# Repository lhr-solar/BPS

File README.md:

# Battery Protection System Code
This repo contains all code related to LHR Solar's Battery Protection System (BPS)
The [Documentation](https://bps.readthedocs.io/en/latest/) for the BPS contains other useful software and an in depth explanation of our architecture.

NOTE: As of 2023, the simulator for the BPS repository is deprecated.

## Setup
Development is done in a Linux environment to build and flash the BPS program.

### Cloning the Repo
Cloning repos onto your machine is usually straightforward, but our RTOS project depend on uCOS-III-Simulator and uCOS-III-STM32F4 repos. Extra steps must be taken to correctly pull submodules. [Submodules](https://git-scm.com/book/en/v2/Git-Tools-Submodules) are repos that are inside a repo.

The most common way to clone repos is to use the HTTPS link, but the most secure way is to clone with SSH. The submodules use SSH, so you must generate and add an SSH key to your GitHub account. Follow the instructions in this tutorial. If this is your first time doing this, you can start at the [Generating a new SSH key and adding it to the ssh-agent](https://docs.github.com/en/github/authenticating-to-github/generating-a-new-ssh-key-and-adding-it-to-the-ssh-agent) step, but reading everything is beneficial.

Once you're able to use Git with SSH, go to the green "Code" button of the repo, and click "Use SSH" to get the URL. Copy the `git@hithub.com:repo-name` link. Then, enter the following command to the terminal but with the correct URL:

```
git clone --recurse-submodules git@github.com:repo-name
```
If you already cloned the repo but don't have the submodules, enter the following commands:

```
git submodule init
git submodule update --remote
```

### Setup for Terminal Development
The BPS is designed be built and deployed from a Linux terminal, allowing you to use your choice of text editor/IDE.
1. Ensure that you have some type of Linux machine such as Ubuntu, Windows Subsystem for Linux, etc. Windows will not work.
    - While you can compile the code on WSL, you will not be able to flash the code unless it is through a Linux machine (VM, dual boot, etc.)
2. The BPS code supports multiple microcontrollers and different architectures. Depending on which on you're using, make sure you have the correct toolchain.
    - STM32F413: Follow the instructions in this [repo](https://github.com/SijWoo/ARM-Toolchain-Setup) to setup the toolchains for the current BPS.
    - Simulator: Install GCC and GDB using the following lines
        ```
        sudo apt install gcc gdb
        ```
3. (Optional) Download [VSCode](https://code.visualstudio.com/)
4. (Optional) In VSCode, download the following extensions (Click on the block icon on the left column):
    - C/C++
    - ARM
    - cortex-debug
5. OPTIONAL: If you are testing on the simulator, you must add the following line in `/etc/security/limits.conf` then restart your machine:
    ```
    <username>             -      rtprio          unlimited
    ```
    The tabbing MUST MATCH the other dashes at the bottom of the file, otherwise this will not work!

## Building
Run `make help` for more information on usage. 
When calling any of the following commands, make sure you are in the top level of the repo.

Call `make bsp_type` to compile the release version of the code. `bsp_type` is the system you want to compile for. It can either be
`stm32f4132` or `simulator`. The stm32f413 version is selected by default.

Call `make help` for more information on how to build the project.

Call `make clean` if the build fails for any reason other than syntax related.

The BPS has an RTOS version and a bare metal version for its BSP files. To select which one to build, pass either `RTOS` or `BAREMETAL` to the `OS` argument. For example
```
make simulator OS=BAREMETAL
```
will build the bare metal version, and  
```
make simulator OS=RTOS
```
will build the RTOS version. The RTOS version is selected by default.

The BPS configuration settings can be modified from the command line from Make. In the top-level of the repo,
you can specify `DEFINES=` alongside the `make` command to override values from the configuration
header file with the values you specify. For example
```
make test=Voltage DEFINES=NUM_MINIONS=2
```
Would update the BPS build to use 2 minion boards in the code and calculations as opposed to 3.
Run `make help` for more information on usage.

For testing, please read the Testing section.

### How to build a test
To build a new test, you need to use the following command:
`make bsp_type TEST=x`

- `x` specifies which test you want to compile. TEST= is optional and only required if a test is to be compiled. Set TEST equal to the suffix of the Test_ Src files i.e. if the test you want to run is in Test_x.c, set TEST=x.
    E.g. Call `make stm32f413 TEST=Voltage` if you want to test Voltage.c with the Test_Voltage.c src file

## Flashing
When calling any of the following commands, make sure you are in the top most level of the directory.
You must be on a Linux VM or dual boot machine. Consider using [VMWARE](https://kb.vmware.com/s/article/2057907) 
using this free license [key](https://gist.github.com/williamgh2019/cc2ad94cc18cb930a0aab42ed8d39e6f)

1. Install `st-util`
2. Connect your computer to the BPS using a Nucleo programmer
3. Call `make flash` to flash the most recently built BPS code. You may need to run this with `sudo`.

## Testing
The following testing information is specifically for terminal development.

### Rules for making a new test Src file
1. Test names: The formatting of the file names is crucial to have the Makefile work properly. "Test_" should be the prefix and the src file name that is to be tested must follow i.e. if you want to test x.c, the test Src file must be named Test_x.c or the Makefile will not be able to find the file.
    E.g. A test for Voltage.c should be Test_Voltage.c file, a test for BSP_SPI.c should be named Test_BSP_SPI.c
2. All test files should be placed into the Tests folder.

### Using GDB with OPENOCD
OpenOCD is a debugger program that is open source and compatible with the STM32F413. 
GDB is a debugger program that can be used to step through a program as it is being run on the board. To use, you need two terminals open, as well as a USB connection to the ST-Link programmer (as if you were going to flash the program to the board). 
1. Run `./openocd-debug.sh` in one terminal.
2. In the other terminal, start gdb with the command `gdb-multiarch ./Objects/bps-leader.elf` (assuming that you are doing this in the root of the project directory.
3. This will launch GDB and read in all of the symbols from the program that you are running on the board. In order to actually connect gdb to the board, execute the command `target extended-remote localhost:4242`, which will connect to the st-util command from earlier.

**Note:** If you get an error message for Permission denied, try giving openocd read/write permissions using chmod: `chmod 764 openocd`

https://linuxcommand.org/lc3_lts0090.php

### Using the Simulator
The simulator reads input from a JSON file to simulate dummy values and dumps output to a log file to simulate controlling the BPS's peripherals. The goal is to create repeatable tests that can be checked automatically by using the same test file, and by parsing the log file.

The simulator can be compiled with `make simulator`. The simulator also has an optional command line argument `TEST=` to specify the name of the test file to run. 

Note: when typing name it, don't type the `Test_` part or the `.c` part.

Example: `make simulator TEST=SimulatorInit`.

The simulator can be run with `./bps-simulator.out <path to JSON test>`. However, in order to run properly, `ulimit -r` must be set from within a script. In order to debug, edit the `test.sh` file
to either debug, or just run a specific test.

You can check the log file by doing `cat bps-sim-<logged time>.log`.

## Rules
Commit frequently into your own branches. Create a Pull Request whenever you are ready to add you working code to the master branch. Make sure that your code compiles without any errors or warnings before you open a pull request. At least one approver must approve your pull request before it can be merged. The reviewers will make sure everything is up to par with the coding standards.

### Code Reviews
You can review a pull request even if you are not an approver. In addition to helping us catch bugs, code reviews are a good opportunity to learn more about the BPS codebase. Some examples on what you can include in a code review are:
- Ask why the author wrote a certain part of code in a way they did
- Point out potential bugs in the code
- Point out that part of the code is not well documented or hard to read

You can either approve, comment, or request changes at the end of your pull request. These are the scenarios in which I would use each option:
- **Approve:** You are signing off that this pull request is ready to merge. You and the pull request author "own" this part of the code now.
- **Request Changes:** You have found problems with the code that must be addressed before it can be merged. Note that this will block the pull request from merging until you re-review the code.
- **Comment:** Do this if you do not want to explicitly approve or request changes.

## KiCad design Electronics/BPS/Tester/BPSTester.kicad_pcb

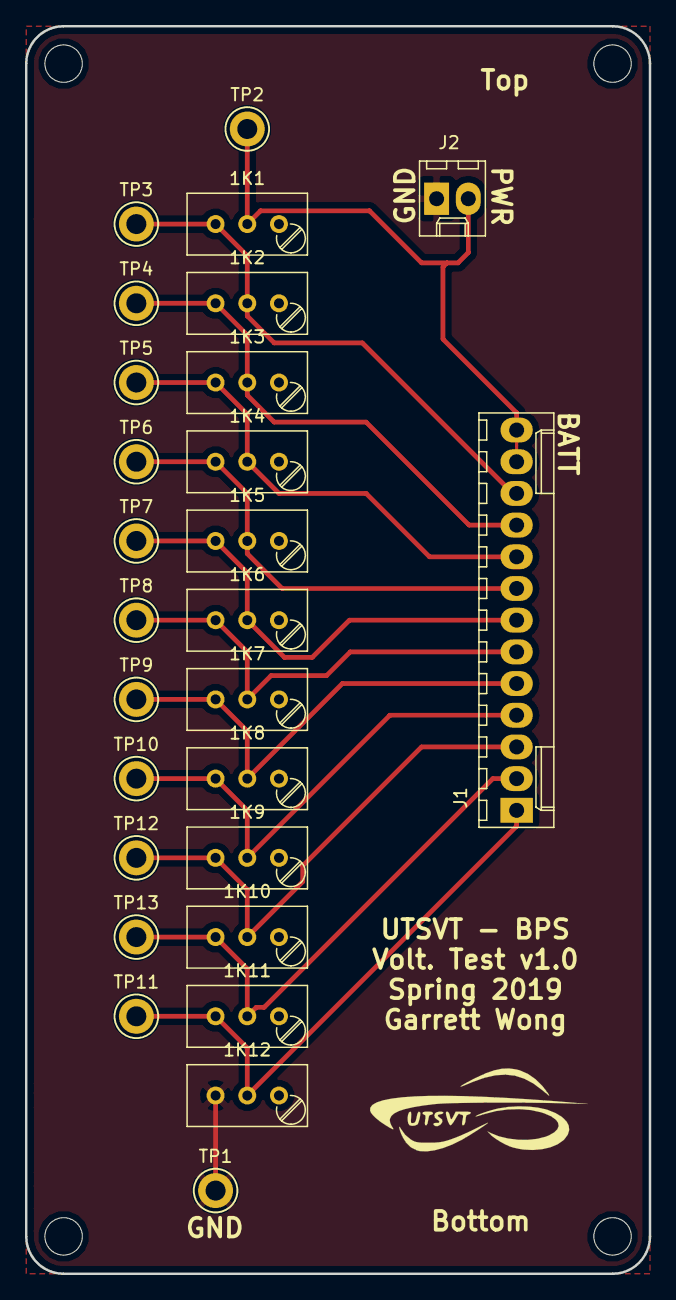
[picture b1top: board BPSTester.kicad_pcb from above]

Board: 2 copper layers, 50.0 x 100.0 mm, 27 parts (0 on the bottom side), 13 nets.

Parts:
1K1, 1K2, 1K3, 1K4, 1K5, 1K6, 1K7, 1K8, 1K9, 1K10, 1K11, 1K12: POT; Potentiometer_Trimmer_Bourns_3296W
J1: Conn_01x13_Male; Molex_KK-6410-13_13x2.54mm_Straight
J2: Conn_01x02_Male; Molex_KK-6410-02_02x2.54mm_Straight
TP1, TP2, TP3, TP4, TP5, TP6, TP7, TP8, TP9, TP10, TP11, TP12, TP13: TestPoint; Test_Point_Keystone_5005-5009_Compact

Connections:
+BATT: 1K1.2, J1.12, J1.13, J2.2, TP2.1
GND: 1K12.3, J2.1, TP1.1
unnamed: 1K1.3, 1K2.2, J1.11, TP3.1
unnamed: 1K2.3, 1K3.2, J1.10, TP4.1
unnamed: 1K3.3, 1K4.2, J1.9, TP5.1
unnamed: 1K4.3, 1K5.2, J1.8, TP6.1
unnamed: 1K5.3, 1K6.2, J1.7, TP7.1
unnamed: 1K6.3, 1K7.2, J1.6, TP8.1
unnamed: 1K7.3, 1K8.2, J1.5, TP9.1
unnamed: 1K8.3, 1K9.2, J1.4, TP10.1
unnamed: 1K9.3, 1K10.2, J1.3, TP12.1
unnamed: 1K10.3, 1K11.2, J1.2, TP13.1
unnamed: 1K11.3, 1K12.2, J1.1, TP11.1

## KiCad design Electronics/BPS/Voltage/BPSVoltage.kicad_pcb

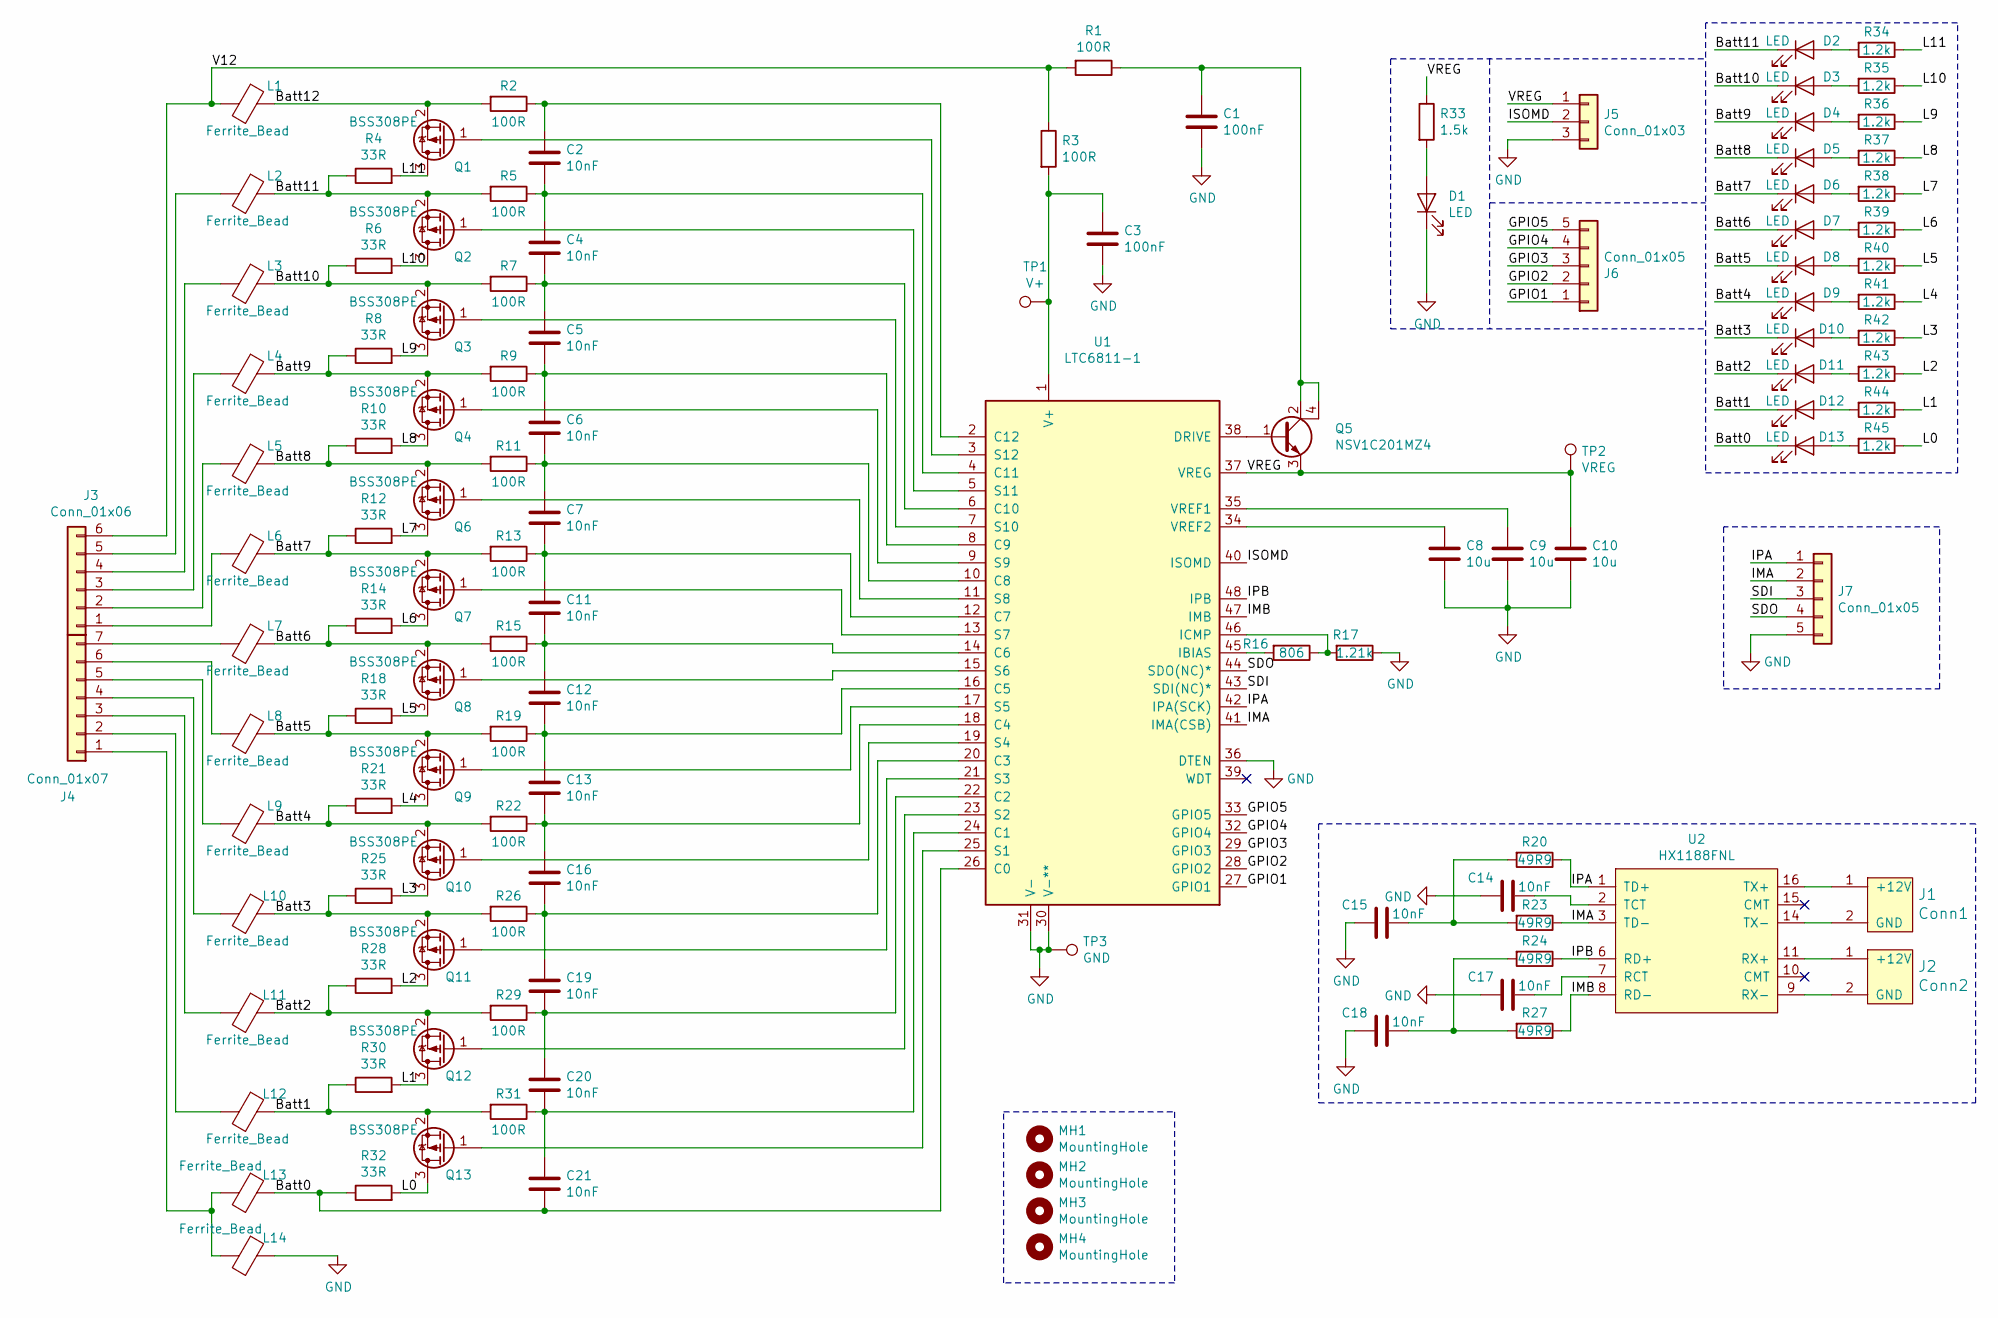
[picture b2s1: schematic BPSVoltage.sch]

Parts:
C1, C3: 100nF; C_0805_2012Metric
C2, C4, C5, C6, C7, C11, C12, C13, C14, C15, C16, C17, C18, C19, C20, C21: 10nF; C_0805_2012Metric
C8, C9, C10: 10u; C_0805_2012Metric
D1, D2, D3, D4, D5, D6, D7, D8, D9, D10, D11, D12, D13: LED; LED_0805_2012Metric
J1: Conn1; Molex_MicroFit3.0_1x2xP3.00mm_PolarizingPeg_Vertical
J2: Conn2; Molex_MicroFit3.0_1x2xP3.00mm_PolarizingPeg_Vertical
J3: Conn_01x06; Molex_MicroFit_01x06_Horizontal
J4: Conn_01x07; Molex_MicroFit_01x07_Horizontal
J5: Conn_01x03; PinHeader_1x03_P2.54mm_Vertical
J6, J7: Conn_01x05; PinHeader_1x05_P2.54mm_Vertical
L1, L2, L3, L4, L5, L6, L7, L8, L9, L10, L11, L12, L13, L14: Ferrite_Bead; L_0805_2012Metric
MH1, MH2, MH3, MH4: MountingHole; MountingHole_3mm
Q1, Q2, Q3, Q4, Q6, Q7, Q8, Q9, Q10, Q11, Q12, Q13: BSS308PE; SOT-23
Q5: NSV1C201MZ4; SOT-223
R1, R2, R3, R5, R7, R9, R11, R13, R15, R19, R22, R26, R29, R31: 100R; R_0805_2012Metric
R4, R6, R8, R10, R12, R14, R18, R21, R25, R28, R30, R32: 33R; R_2512_6332Metric
R16: 806; R_0805_2012Metric
R17: 1.21k; R_0805_2012Metric
R20, R23, R24, R27: 49R9; R_0805_2012Metric
R33: 1.5k; R_0805_2012Metric
R34, R35, R36, R37, R38, R39, R40, R41, R42, R43, R44, R45: 1.2k; R_0805_2012Metric
TP1: V+; TestPoint_Keystone_5005-5009_Compact
TP2: VREG; TestPoint_Keystone_5005-5009_Compact
TP3: GND; TestPoint_Keystone_5005-5009_Compact
U1: LTC6811-1; SSOP-48_7.5x15.9mm_P0.635mm
U2: HX1188FNL; HXXXX

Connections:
/Batt0: C21.1, D13.1 (K), L13.1, R32.1, U1.26 (C0)
/Batt1: D12.1 (K), L12.1, Q13.2 (S), R30.1, R31.2
/Batt2: D11.1 (K), L11.1, Q12.2 (S), R28.1, R29.2
/Batt3: D10.1 (K), L10.1, Q11.2 (S), R25.1, R26.2
/Batt4: D9.1 (K), L9.1, Q10.2 (S), R21.1, R22.2
/Batt5: D8.1 (K), L8.1, Q9.2 (S), R18.1, R19.2
/Batt6: D7.1 (K), L7.1, Q8.2 (S), R14.1, R15.2
/Batt7: D6.1 (K), L6.1, Q7.2 (S), R12.1, R13.2
/Batt8: D5.1 (K), L5.1, Q6.2 (S), R10.1, R11.2
/Batt9: D4.1 (K), L4.1, Q4.2 (S), R8.1, R9.2
/Batt10: D3.1 (K), L3.1, Q3.2 (S), R6.1, R7.2
/Batt11: D2.1 (K), L2.1, Q2.2 (S), R4.1, R5.2
/Batt12: L1.1, Q1.2 (S), R2.2
/GPIO1: J6.1, U1.27 (GPIO1)
/GPIO2: J6.2, U1.28 (GPIO2)
/GPIO3: J6.3, U1.29 (GPIO3)
/GPIO4: J6.4, U1.32 (GPIO4)
/GPIO5: J6.5, U1.33 (GPIO5)
/IMA: J7.2, R23.1, U1.41 (IMA(CSB)), U2.3 (TD-)
/IMB: R27.1, U1.47 (IMB), U2.8 (RD-)
/IPA: J7.1, R20.1, U1.42 (IPA(SCK)), U2.1 (TD+)
/IPB: R24.1, U1.48 (IPB), U2.6 (RD+)
/ISOMD: J5.2, U1.40 (ISOMD)
/L0: Q13.3 (D), R32.2, R45.1
/L1: Q12.3 (D), R30.2, R44.1
/L2: Q11.3 (D), R28.2, R43.1
/L3: Q10.3 (D), R25.2, R42.1
/L4: Q9.3 (D), R21.2, R41.1
/L5: Q8.3 (D), R18.2, R40.1
/L6: Q7.3 (D), R14.2, R39.1
/L7: Q6.3 (D), R12.2, R38.1
/L8: Q4.3 (D), R10.2, R37.1
/L9: Q3.3 (D), R8.2, R36.1
/L10: Q2.3 (D), R6.2, R35.1
/L11: Q1.3 (D), R4.2, R34.1
/SDI: J7.3, U1.43 (SDI(NC)*)
/SDO: J7.4, U1.44 (SDO(NC)*)
/V12: J3.6, L1.2, R1.2, R3.1
/VREG: C10.1, J5.1, Q5.3 (E), R33.1, TP2.1, U1.37 (VREG)
GND: C1.2, C3.2, C8.2, C9.2, C10.2, C14.2, C15.2, C17.2, C18.2, D1.1 (K), J5.3, J7.5, L14.1, R17.1, TP3.1, U1.30 (V-**), U1.31 (V-), U1.36 (DTEN)
unnamed: C1.1, Q5.2 (C), Q5.4 (C), R1.1
unnamed: C2.1, C4.2, R5.1, U1.4 (C11)
unnamed: C2.2, R2.1, U1.2 (C12)
unnamed: C3.1, R3.2, TP1.1, U1.1 (V+)
unnamed: C4.1, C5.2, R7.1, U1.6 (C10)
unnamed: C5.1, C6.2, R9.1, U1.8 (C9)
unnamed: C6.1, C7.2, R11.1, U1.10 (C8)
unnamed: C8.1, U1.34 (VREF2)
unnamed: C9.1, U1.35 (VREF1)
unnamed: C11.1, C12.2, R15.1, U1.14 (C6)
unnamed: C7.1, C11.2, R13.1, U1.12 (C7)
unnamed: C12.1, C13.2, R19.1, U1.16 (C5)
unnamed: C13.1, C16.2, R22.1, U1.18 (C4)
unnamed: C14.1, U2.2 (TCT)
unnamed: C15.1, R20.2, R23.2
unnamed: C16.1, C19.2, R26.1, U1.20 (C3)
unnamed: C17.1, U2.7 (RCT)
unnamed: C18.1, R24.2, R27.2
unnamed: C19.1, C20.2, R29.1, U1.22 (C2)
unnamed: C20.1, C21.2, R31.1, U1.24 (C1)
unnamed: D1.2 (A), R33.2
unnamed: D2.2 (A), R34.2
unnamed: D3.2 (A), R35.2
unnamed: D4.2 (A), R36.2
unnamed: D5.2 (A), R37.2
unnamed: D6.2 (A), R38.2
unnamed: D7.2 (A), R39.2
unnamed: D8.2 (A), R40.2
unnamed: D9.2 (A), R41.2
unnamed: D10.2 (A), R42.2
unnamed: D11.2 (A), R43.2
unnamed: D12.2 (A), R44.2
unnamed: D13.2 (A), R45.2
unnamed: J1.1 (+12V), U2.16 (TX+)
unnamed: J1.2 (GND), U2.14 (TX-)
unnamed: J2.1 (+12V), U2.11 (RX+)
unnamed: J2.2 (GND), U2.9 (RX-)
unnamed: J3.1, L6.2
unnamed: J3.2, L5.2
unnamed: J3.3, L4.2
unnamed: J3.4, L3.2
unnamed: J3.5, L2.2
unnamed: J4.1, L13.2, L14.2
unnamed: J4.2, L12.2
unnamed: J4.3, L11.2
unnamed: J4.4, L10.2
unnamed: J4.5, L9.2
unnamed: J4.6, L8.2
unnamed: J4.7, L7.2
unnamed: Q1.1 (G), U1.3 (S12)
unnamed: Q2.1 (G), U1.5 (S11)
unnamed: Q3.1 (G), U1.7 (S10)
unnamed: Q4.1 (G), U1.9 (S9)
unnamed: Q5.1 (B), U1.38 (DRIVE)
unnamed: Q6.1 (G), U1.11 (S8)
unnamed: Q7.1 (G), U1.13 (S7)
unnamed: Q8.1 (G), U1.15 (S6)
unnamed: Q9.1 (G), U1.17 (S5)
unnamed: Q10.1 (G), U1.19 (S4)
unnamed: Q11.1 (G), U1.21 (S3)
unnamed: Q12.1 (G), U1.23 (S2)
unnamed: Q13.1 (G), U1.25 (S1)
unnamed: R16.1, R17.2, U1.46 (ICMP)
unnamed: R16.2, U1.45 (IBIAS)

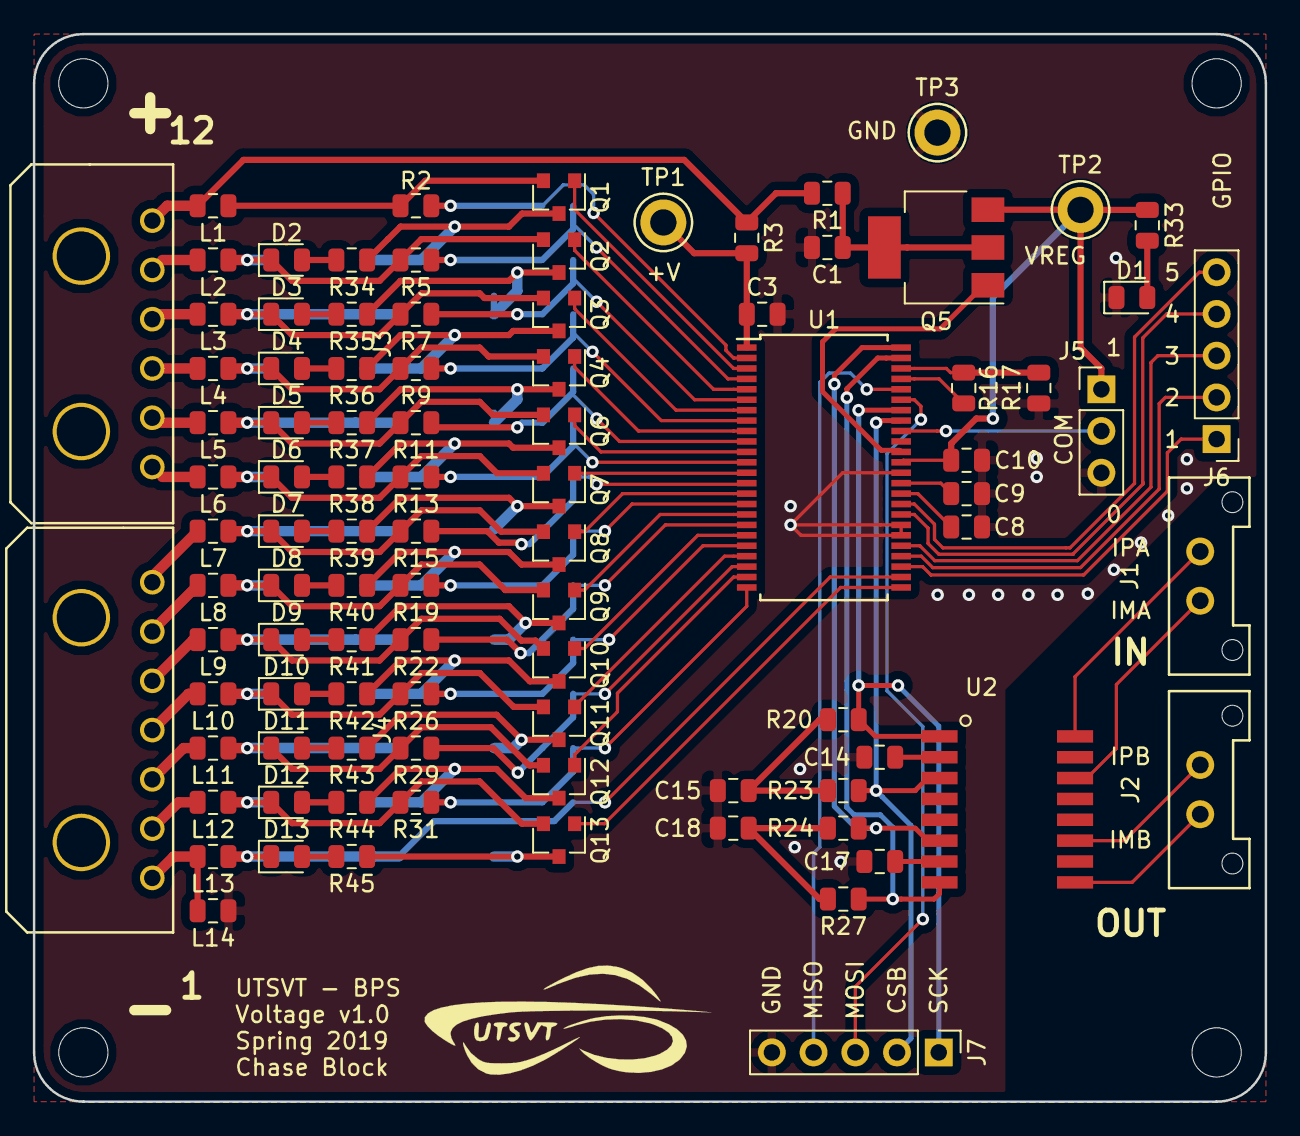
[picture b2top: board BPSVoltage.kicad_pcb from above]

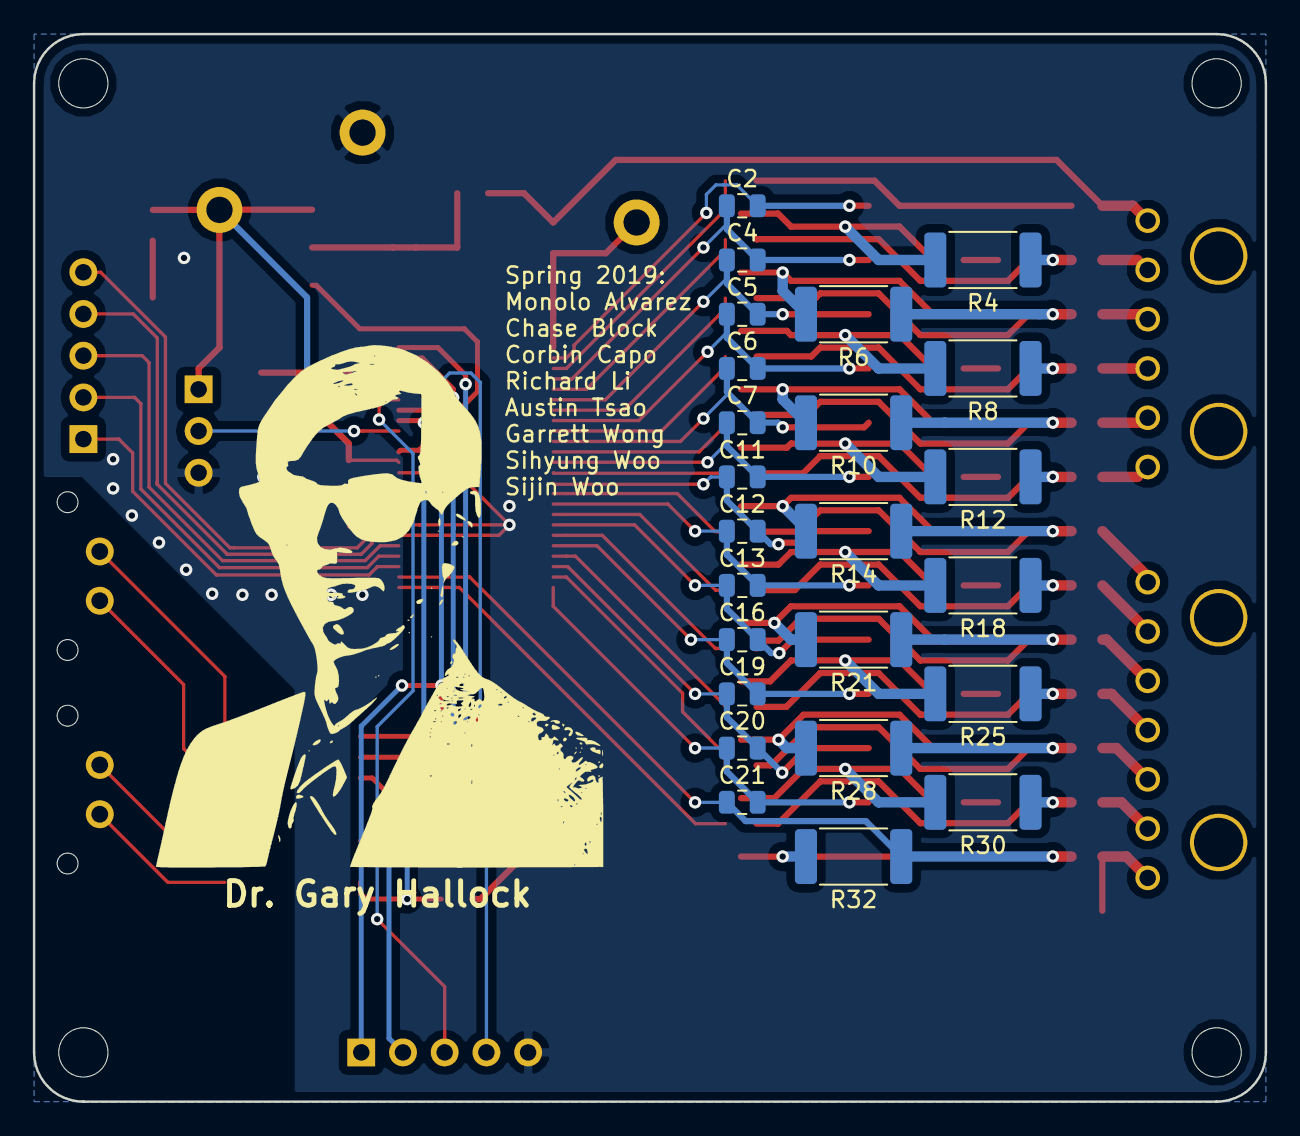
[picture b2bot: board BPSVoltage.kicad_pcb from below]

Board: 2 copper layers, 75.0 x 65.0 mm, 118 parts (24 on the bottom side), 104 nets.

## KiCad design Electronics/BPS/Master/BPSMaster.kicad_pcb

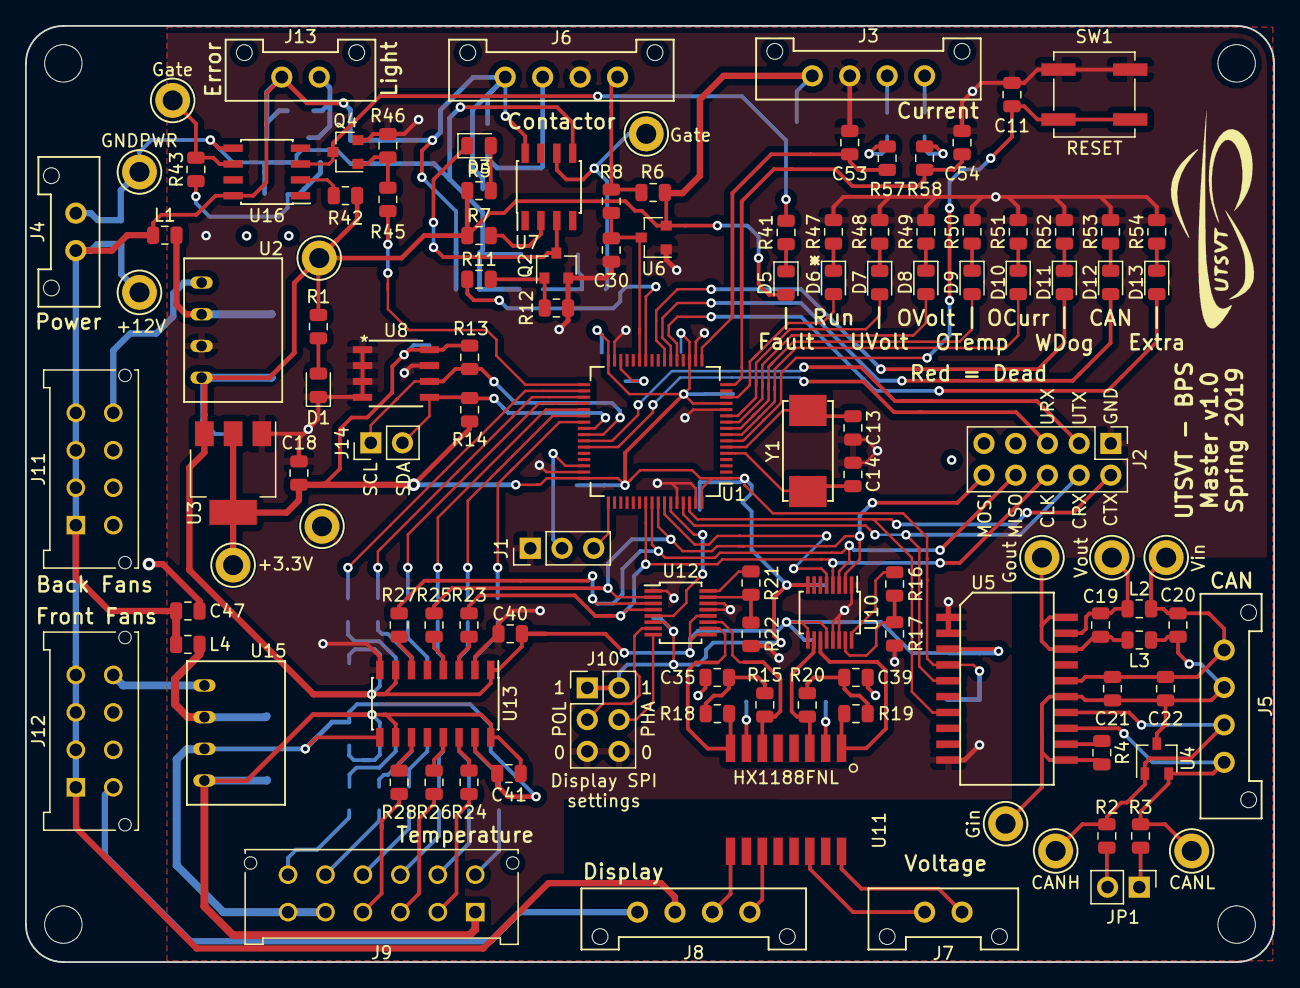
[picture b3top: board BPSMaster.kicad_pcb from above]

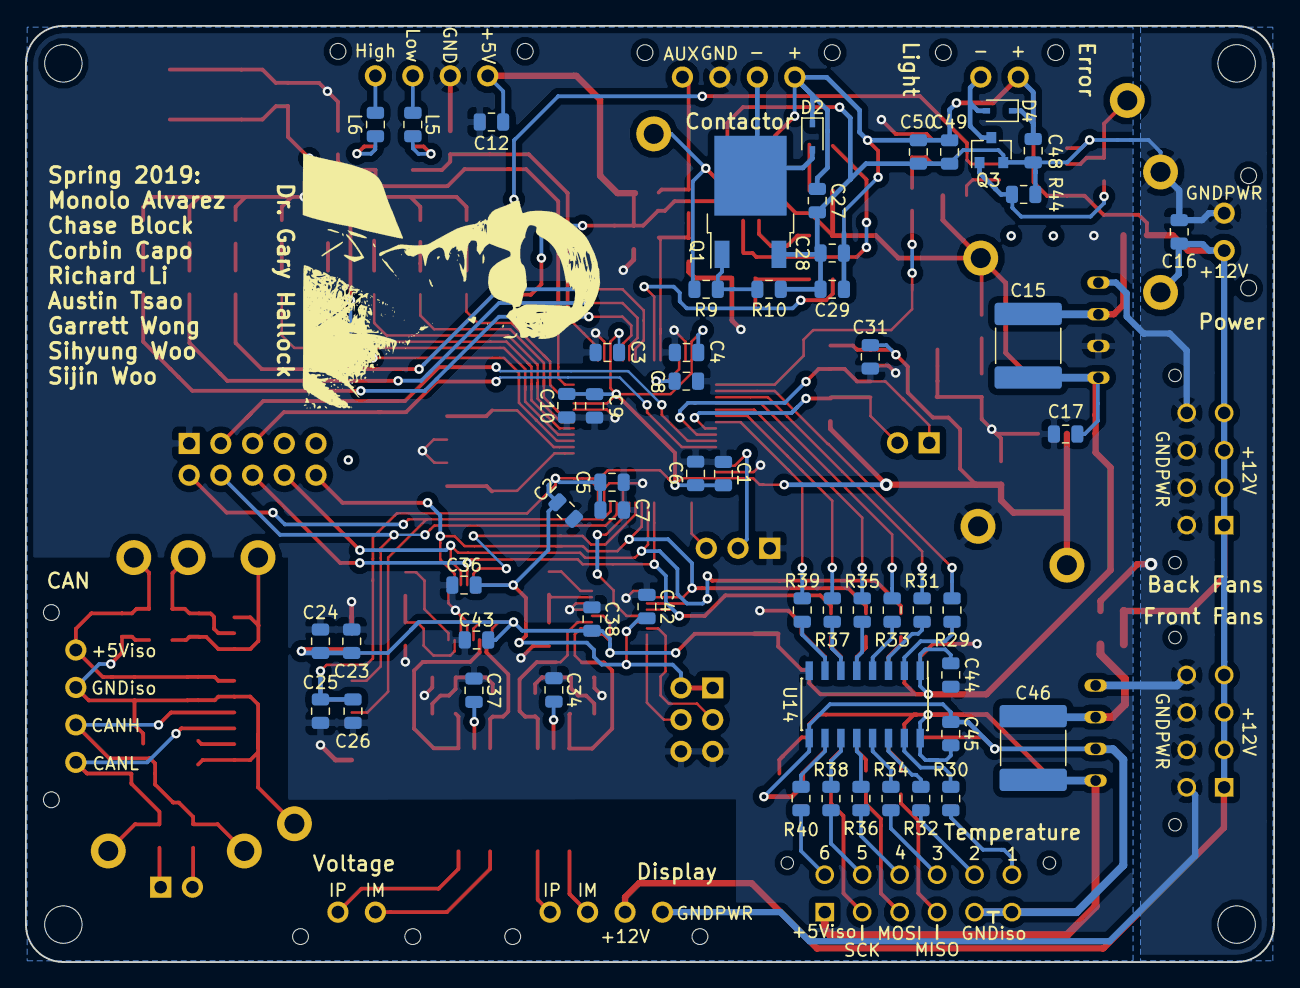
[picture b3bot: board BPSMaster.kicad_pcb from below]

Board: 2 copper layers, 100.0 x 75.0 mm, 178 parts (56 on the bottom side), 127 nets.

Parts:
C1, C2, C3, C4, C5, C6, C9, C11, C12, C17, C21, C24, C25, C29, C31, C36, C38, C40, C41, C42, C43, C44, C45, C50: 0.1uF; C_0805_2012Metric
C7, C16, C47: 4.7uF; C_0805_2012Metric
C8: 2.2uF; C_0805_2012Metric
C10, C27, C30, C48, C53, C54: 1uF; C_0805_2012Metric
C13, C14: 6pF; C_0805_2012Metric
C15, C46: 470pF; C_2220_5650Metric
C18, C19, C23, C28, C49: 10uF; C_0805_2012Metric
C20: 0.22uF; C_0805_2012Metric
C22, C26, C34, C35, C37, C39: 0.01uF; C_0805_2012Metric
D1: PowerOn; LED_0805_2012Metric
D2, D4: 1N4148WS; D_SOD-323
D3: ContactorEn; LED_0805_2012Metric
D5: Fault; LED_0805_2012Metric
D6: Heartbeat; LED_0805_2012Metric
D7: UVolt; LED_0805_2012Metric
D8: OVolt; LED_0805_2012Metric
D9: OTemp; LED_0805_2012Metric
D10: OCurr; LED_0805_2012Metric
D11: WDError; LED_0805_2012Metric
D12: CANError; LED_0805_2012Metric
D13: Extra; LED_0805_2012Metric
J1: SWD; PinHeader_1x03_P2.54mm_Vertical
J2: Logic Analyzer; PinHeader_2x05_P2.54mm_Vertical
J3: CurrentSlaveConnector; Molex_MicroFit3.0_1x4xP3.00mm_PolarizingPeg_Vertical
J4: CarPowerConnector; Molex_MicroFit3.0_1x2xP3.00mm_PolarizingPeg_Vertical
J5: CAN_Out; Molex_MicroFit3.0_1x4xP3.00mm_PolarizingPeg_Vertical
J6: ContactorConnector; Molex_MicroFit3.0_1x4xP3.00mm_PolarizingPeg_Vertical
J7: VoltageSlaveConnector; Molex_MicroFit3.0_1x2xP3.00mm_PolarizingPeg_Vertical
J8: DisplayConnector; Molex_MicroFit3.0_1x4xP3.00mm_PolarizingPeg_Vertical
J9: TempSlaveConnector; Molex_MicroFit3.0_2x6xP3.00mm_PolarizingPeg_Vertical
J10: DisplayJumper; PinHeader_2x03_P2.54mm_Vertical
J11: FrontFans; Molex_MicroFit3.0_2x4xP3.00mm_PolarizingPeg_Vertical
J12: BackFans; Molex_MicroFit3.0_2x4xP3.00mm_PolarizingPeg_Vertical
J13: ErrorLightConnector; Molex_MicroFit3.0_1x2xP3.00mm_PolarizingPeg_Vertical
J14: Conn_01x03; PinHeader_1x02_P2.54mm_Vertical
JP1: Termination Resistors; PinHeader_1x02_P2.54mm_Vertical
L1, L4: 10uH; L_0805_2012Metric
L2, L3: 2kH; L_0805_2012Metric
L5, L6: 600; L_0805_2012Metric
MH1, MH2, MH3, MH4: MountingHole; MountingHole_3mm
Q1: VND5N07-E; TO-252-2
Q2, Q3, Q4: NVR4003NT3G; SOT-23
R1, R5: 1.5k; R_0805_2012Metric
R2, R3: 60; R_0805_2012Metric
R4, R9, R11, R43, R45: 0; R_0805_2012Metric
R6, R13, R14: 4.7k; R_0805_2012Metric
R7, R42: 470; R_0805_2012Metric
R8: 1k; R_0805_2012Metric
R10, R12, R44, R46: 100k; R_0805_2012Metric
R15, R18, R19, R20: 49.9; R_0805_2012Metric
R16, R21: 806; R_0805_2012Metric
R17, R22: 1.21k; R_0805_2012Metric
R23, R24, R25, R26, R27, R28, R29, R30, R31, R32, R33, R34, R35, R36, R37, R38, R39, R40: 50; R_0805_2012Metric
R41: 1.6k; R_0805_2012Metric
R47: 680; R_0805_2012Metric
R48, R49, R50, R51, R52, R53, R54: 750; R_0805_2012Metric
R57, R58: 220k; R_0805_2012Metric
SW1: B3SL-1002P; SW_SPST_B3SL-1002P
TP1: +12V_TP; TestPoint_Keystone_5005-5009_Compact
TP2: +5V_TP; TestPoint_Keystone_5005-5009_Compact
TP3: GND_TP; TestPoint_Keystone_5005-5009_Compact
TP4: +3.3V_TP; TestPoint_Keystone_5005-5009_Compact
TP5: CAN_ISO_Vout; TestPoint_Keystone_5005-5009_Compact
TP6: CAN_ISO_Vin; TestPoint_Keystone_5005-5009_Compact
TP7: CAN_ISO_GndIn; TestPoint_Keystone_5005-5009_Compact
TP8: CAN_ISO_GndOut; TestPoint_Keystone_5005-5009_Compact
TP9: CAN_H; TestPoint_Keystone_5005-5009_Compact
TP12: CAN_L; TestPoint_Keystone_5005-5009_Compact
TP13: ContactorGate_TP; TestPoint_Keystone_5005-5009_Compact
TP14: StrobeLightGate_TP; TestPoint_Keystone_5005-5009_Compact
TP15: GNDPWR_TP; TestPoint_Keystone_5005-5009_Compact
U1: STM32F413RHTx; LQFP-64_10x10mm_P0.5mm
U2, U15: RI3-1205S; RI3_DC_Converter
U3: NCP1117-3.3_SOT223; SOT-223-3_TabPin2
U4: CDSOT23-T24CAN; SOT-23W
U5: ADM3055E; SOIC-20W_7.5x15.4mm_Pitch1.27mm
U6: BAS70-04; SOT-23
U7, U16: SI8261ABC-IS; SOIC-8_3.9x4.9mm_P1.27mm
U8: M24128; M24128-BRMN6P
U10, U12: LTC6820; MSOP-16_3x4mm_P0.5mm
U11: HX1188FNL; HXXXX
U13: Si8641EC-B-IS1; SOIC-16_3.9x9.9mm_P1.27mm
U14: SI8660EC-B-IS1; SOIC-16_3.9x9.9mm_P1.27mm
Y1: NX8045GB-8.000M-STD-CSJ-1

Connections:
+3V3: C1.1, C2.1, C3.1, C4.1, C5.1, C6.1, C7.1, C9.1, C10.1, C18.1, C25.1, C26.1, C31.1, C36.1, C42.1, J10.1, J10.2, R13.1, R14.1, TP4.1, U1.1, U1.13, U1.19, U1.32, U1.48, U1.64, U3.2, U5.4, U8.8, U10.6, U10.7, U10.8, U12.6
+5V: C12.2, C15.2, C17.1, C23.1, C24.1, C38.1, C40.1, C43.1, C44.1, D5.2, J3.1, R1.1, R5.1, R6.2, R7.2, R42.2, TP2.1, U2.4, U3.3, U5.3, U6.2, U10.9, U10.12, U12.9, U12.12, U13.1, U13.7, U14.1
+5VL: C41.1, C45.1, C46.2, J9.1, U13.10, U13.16, U14.16, U15.4
+12V: C16.1, C27.2, C28.1, C29.1, C47.1, C48.2, C49.1, C50.1, D2.1, D4.1, J4.1, J6.1, J8.3, J11.1, J11.2, J11.3, J11.4, J12.1, J12.2, J12.3, J12.4, J13.1, L1.1, L4.1, TP1.1, U7.8, U16.8
/ADC1_CH2: C54.1, R58.2, U1.16
/ADC1_CH3: C53.1, R57.2, U1.17
/CAN1_RX: J2.4, U1.61, U5.5
/CAN1_TX: J2.2, U1.62, U5.7
/CAN/CAN_H: J5.3, R2.2, TP9.1, U4.1, U5.14
/CAN/CAN_L: J5.4, R3.2, TP12.1, U4.2, U5.13
/CAN/RSlope: R4.1, U5.12
/CAN/TERM_H: JP1.2, R2.1
/CAN/TERM_L: JP1.1, R3.1
/Contactor Driver/CONTACTOR_V-: D2.2, J6.2, Q1.2
/DISPLAY_CS: U1.59, U12.5
/FAULT: R45.2, U1.33
/I2C3_SCL: J14.1, R13.2, U1.41, U8.6
/I2C3_SDA: J14.2, R14.2, U1.40, U8.5
/LTC6811_CS: U1.58, U10.5
/NRST: C11.1, SW1.1, U1.7
/OSC_IN: C14.1, U1.5, Y1.2
/OSC_OUT: C13.1, U1.6, Y1.1
/PA5: D13.2, U1.21
/PA6: D12.2, U1.22
/PA7: D11.2, U1.23
/PB0: R11.2, U1.26
/PB1: C30.1, R8.1, U1.27, U6.3
/PC0: D10.2, U1.8
/PC1: D9.2, U1.9
/PC2: D8.2, U1.10
/PC3: D7.2, U1.11
/RUN: D6.2, U1.14
/SPI1_CLK: J2.6, R23.2, U1.55, U10.4, U12.4
/SPI1_MISO: J2.8, R27.2, U1.56, U10.3, U12.3
/SPI1_MOSI: J2.10, R25.2, U1.57, U10.2, U12.2
/SPI/CS1: J9.12, R30.1
/SPI/CS2: J9.11, R32.1
/SPI/CS3: J9.10, R34.1
/SPI/CS4: J9.9, R36.1
/SPI/CS5: J9.8, R38.1
/SPI/CS6: J9.7, R40.1
/SPI/DISP_IM: R18.1, U11.8, U12.10
/SPI/DISP_IP: R15.1, U11.6, U12.11
/SPI/DISP_PHA: J10.4, U12.8
/SPI/DISP_POL: J10.3, U12.7
/SPI/VOLT_IM: R20.1, U10.10, U11.3
/SPI/VOLT_IP: R19.1, U10.11, U11.1
/SWCLK: J1.3, U1.49
/SWDIO: J1.2, U1.46
/TEMP_CS1: R29.1, U1.34
/TEMP_CS2: R31.1, U1.35
/TEMP_CS3: R33.1, U1.36
/TEMP_CS4: R35.1, U1.37
/TEMP_CS5: R37.1, U1.38
/TEMP_CS6: R39.1, U1.39
/UART1_RX: J2.5, U1.43
/UART1_TX: J2.3, U1.42
GND: C1.2, C2.2, C3.2, C4.2, C5.2, C6.2, C7.2, C8.2, C9.2, C10.2, C11.2, C12.1, C13.2, C14.2, C17.2, C18.2, C23.2, C24.2, C25.2, C26.2, C30.2, C31.2, C34.2, C35.2, C36.2, C37.2, C38.2, C39.2, C40.2, C42.2, C43.2, C44.2, C53.2, C54.2, D1.1, J1.1, J2.1, J3.2, J6.3, J10.5, J10.6, Q2.2, Q4.2, R12.2, R17.1, R22.1, R46.2, R47.2, R48.2, R49.2, R50.2, R51.2, R52.2, R53.2, R54.2, SW1.2, TP3.1, U1.12, U1.18, U1.31, U1.47, U1.60, U1.63, U2.3, U3.1, U5.1, U5.2, U5.10, U6.1, U8.1, U8.2, U8.3, U8.4, U8.7, U10.1, U10.13, U10.14, U12.1, U12.13, U12.14, U13.2, U13.8, U14.8
GNDPWR: C16.2, C27.1, C28.2, C29.2, C47.2, C48.1, C49.2, C50.2, J4.2, J8.4, J11.5, J11.6, J11.7, J11.8, J12.5, J12.6, J12.7, J12.8, Q1.3, Q3.2, R10.2, R44.2, TP15.1, U2.1, U7.5, U15.1, U16.5
GND_A: C41.2, C45.2, J9.5, J9.6, U13.9, U13.15, U14.9, U15.3
unnamed: C8.1, U1.30
unnamed: C15.1, L1.2, U2.2
unnamed: C19.1, L2.2, TP5.1, U5.19
unnamed: C19.2, L3.2, TP8.1, U5.18, U5.20
unnamed: C20.1, C21.1, C22.1, J5.1, L2.1, TP6.1, U5.16
unnamed: C20.2, C21.2, C22.2, J5.2, L3.1, R4.2, TP7.1, U4.3, U5.11, U5.15
unnamed: C34.1, U11.7
unnamed: C35.1, R15.2, R18.2
unnamed: C37.1, U11.2
unnamed: C39.1, R19.2, R20.2
unnamed: C46.1, L4.2, U15.2
unnamed: D1.2, R1.2
unnamed: D3.1, Q2.3, U7.3
unnamed: D3.2, R5.2
unnamed: D4.2, J13.2, Q3.3
unnamed: D5.1, R41.1
unnamed: D6.1, R47.1
unnamed: D7.1, R48.1
unnamed: D8.1, R49.1
unnamed: D9.1, R50.1
unnamed: D10.1, R51.1
unnamed: D11.1, R52.1
unnamed: D12.1, R53.1
unnamed: D13.1, R54.1
unnamed: J3.3, L5.1
unnamed: J3.4, L6.1
unnamed: J6.4, R6.1, R8.2
unnamed: J7.1, U11.16
unnamed: J7.2, U11.14
unnamed: J8.1, U11.11
unnamed: J8.2, U11.9
unnamed: J9.2, R24.2
unnamed: J9.3, R26.2
unnamed: J9.4, R28.2
unnamed: L5.2, R57.1
unnamed: L6.2, R58.1
unnamed: Q1.1, R9.1, R10.1
unnamed: Q2.1, R11.1, R12.1
unnamed: Q3.1, R43.1, R44.1
unnamed: Q4.1, R45.1, R46.1
unnamed: Q4.3, R41.2, U16.3
unnamed: R7.1, U7.2
unnamed: R9.2, TP13.1, U7.6
unnamed: R16.1, R17.2, U10.15
unnamed: R16.2, U10.16
unnamed: R21.1, R22.2, U12.15
unnamed: R21.2, U12.16
unnamed: R23.1, U13.3
unnamed: R24.1, U13.14
unnamed: R25.1, U13.4
unnamed: R26.1, U13.13
unnamed: R27.1, U13.6
unnamed: R28.1, U13.11
unnamed: R29.2, U14.2
unnamed: R30.2, U14.15
unnamed: R31.2, U14.3
unnamed: R32.2, U14.14
unnamed: R33.2, U14.4
unnamed: R34.2, U14.13
unnamed: R35.2, U14.5
unnamed: R36.2, U14.12
unnamed: R37.2, U14.6
unnamed: R38.2, U14.11
unnamed: R39.2, U14.7
unnamed: R40.2, U14.10
unnamed: R42.1, U16.2
unnamed: R43.2, TP14.1, U16.6

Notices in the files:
parts and their libraries:
Copyright 2016 Accelerated Designs. All rights reserved.
